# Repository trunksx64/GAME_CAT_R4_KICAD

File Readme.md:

# Game//Cat ::: Revisión R4 :: Versión 4.2.2

## Razón e Inspiración

El Game//Cat R4 es la evolución del microcontrolador de 16Bits a 32Bits, mas específicamente del PIC24H al ATSAMD21 como núcleo de control, al igual que su antecesor la idea de esta tarjeta y/ó control de desarrollo es usar dispositivos específicos para el aprendizaje, bricolaje y Hobby para proyectos abiertos o de diseño cerrado, el Hardware el Libre con la posibilidad de adaptarlo, modificarlo, cambiarlo a necesidad, claramente respetando al original. El ATSAMD21 es un microcontrolador Originalmente diseñado por ATMEL que utiliza un Nucleo ARM 0M+ dando la ventaja de ser un microcontrolador fácil de usar con Módulos flexibles y robustos, con documentación abundante tanto por lo Comunidad de ARDUINO y la empresa Microchip en este momento. Se diseñó empleando de forma similar la apariencia del Game//Cat R3, agregando mejoras y eliminando errores del anterior, por lo cual es 100% compatible a nivel de diseño.

El ATSAMD21 es compatible en este momento con Microchip Studio (Atmel Studio) y MPLABX V5.0, tanto con GCC y XC32, para programarlo se puede usar ATMEL ICE, MPLAB SNAP, PICKIT4 y El ICD4, Se planea usar el Bootloader original de ARDUINO Zero en un futuro.

Algunos Elementos "Footprints" y "Symbols" están basados en mis librerías, cuáles encontrarán en este mismo Repositorio.

## Características del Hardware

  * Microcontrolador ATSAMD21.
  * Pantalla LCD PCD8544 (Based Nokia GLCD) - SPI.
  * Joystick Análogo de 2 ejes + Botón Digital.
  * 6 Botones Digitales.
  * Accelerometro - MMA8452Q - I2C. 
  * Sensor de Temperatura (LM61).
  * Sensor de Luz (LDR).
  * Memoria Eeprom 24LCXXX - I2C.
  * Memoria Ram 23KXX - SPI.
  * Memoria Flash SST26VF032B - SPI.
  * Ranura Memoria Micro-SD - SPI.
  * Buzzer por PWM.
  * Conexión USB - Nativa por el ATSAM.
  * Conexión CAN-FD - MCP2518FD.
  * 2 LED´s de Actividad.
  * Salidas Para PWM y UART - Con figurables - 3.3V.
  * Conexión SWD Nativa para Debuger.
  * Cargador de Batería Lipo (MCP73831) con Indicador LED.
  * Regulación 3.3V mediante TPS54231.

## Características Específicas

* Para garantizar el control y tensión correspondiente para el uso de BUS CAN, se utiliza el Transeiver MCP2562FD en conjunto del CI MCP2518FD, haciendo compatible el Control con la última version del protocolo CAN.

* Para Potabilidad he agregado un control para la carga de Baterías de tipo Lipo, este gobernado él con el CI MCP73831, el cual intercambia la alimentación proveniente del conector USB y la Batería según el estado de conexión, se puede usar Baterías de 3,7V en adelante hasta un máximo de 6V, se agregó un interruptor para porder desconectar la Batería en modo portable, para evitar su descarga prologanda.

* Para el Manejo del Joystick, Botones, he empleado el CI-74HC4051, que es un Multiplexor Análogo para leer los Valores por el módulo ADC, el cual puede usarse de 10 o 12Bits en conjunto con un canal DMA si fuere necesario.

* La Comunicación por algunos de los Módulos SERCOM disponibles en los conectores Molex, posee un conversor de tensión de 3.3V a 5V de forma bidireccional con transistores Mosfet, con el fin de proteger y poder comunicar el ATSAMD21 con cualquier tipo de dispositivo.

* La Comunicación USB está dedicada por el mismo ATSAMD21, por lo que es necesario programar el Stack propio, este microcontrolador posee una enorme flexibilidad para configurar impactando de forma mínima los recursos. Es posible utilizar el Bootloader del Arduino Zero con algunas modificaciones, aún está en planes de creación, recomiendo emplear el código Generado por AMTEL START, para simplificar las configuraciones tanto de este Módulo como otros Periféricos.

* La Ranura para la Tarjeta Micro-SD, posee conexión Módulo SPI la cual esta compartida con la Memoria Ram 23Kxxx y Memoria Flash SST26VF032B, Además la pantalla posee también una conexión al segundo Módulo SPI, que puede usarse para "colgar" otros dispositivos si no vamos a usar la Pantalla.

* El control del Buzzer se ha dejado por un Pin que puede ser usado tanto por el Modulo PWM o un pin Común, su uso dependerá del Programa o Aplicación.

* Posee una Memoria I2C en conjunto con un Accelerometro, con comunicación directa.

* Los sensores de Luminosidad y Temperatura están conectados directamente a entradas Analógicas del ATSAMD21, no siendo necesario utilizar le MUX 74HC4051.

* La programación se hace por medio de la conexión ICSP o Bootloader por USB, empleando cualquier programador reciente como el ICD4, PICKIT4, SNAP o ATMEL ICE, igual estas salidas pueden usarse como cualquier puerto, teniendo presente que no poseen ninguna protección a tensiones superiores de 3,3V.

* Ya por Último, he dejado dos visualiza-dores, que usan los pines asignados para la Programación del ATSAMD21, controlados por Mosfets para no interferir con el protocolo SWD, su uso está condicionado fuera del Debug.

## Microcontrolador

  * Microcontrolador ATSAMD21 ARM 0M+ de 32Bits.
  * 256KB of flash and 32KB of SRAM.
  * Up to 48MHz operating frequency.
  * Six serial communication modules (SERCOM) configurable as UART/USART, SPI or I2C, three 16-bit timer/counters, 32-bit Real-Time Clock and calendar, 20 PWM channels, one 14-channel 12-bit ADC, one 10-bit DAC.
  * Full Speed USB Device and embedded Host.
  * 1.62V to 3.63V power supply.
  * Internal and external clock options with 48MH Digital Frequency Locked Loop (DFLL48M) and 48MHto 96MHFractional.
  * Two-pin Serial Wire Debug (SWD) programming, test and debugging interface.
  * 38 GPIO pins.
  * 10-bit, 350ksps Digital-to-Analog Converter (DAC).
  * CRC-32 generator.
  * 32-bit Real Time Counter (RTC) with clock/calendar function.
  * Generation of synchronized pulse width modulation (PWM) pattern across port pins.

## Versiones

* 2021 : 4.0.0 : Primera Versión de Diseño.
* 2021 : 4.0.1 : Mirgración completa a Kicad V6, actualización del Libreias y Logos de Diseño.
* 2021 : 4.1.0 : Cambio de Botones Pasantes a SDM.
* 2021 : 4.1.2 : Conectores Moles de tres pines a cuatro pines para Alimentación externar de dispositivos.
* 2021 : 4.1.3 : Correción y cambio de puerto de Programación SWD RJ11 a Header 2x3, similar al AVR SPI.
* 2021 : 4.1.4 : Cambio de Resistencias del conversor de nivel 5V-3.3V de 1K a 10K.
* 2022 : 4.1.5 : Se agregó Interruptor de Encendio por Batería con control Mosfet.
* 2024 : 4.1.6 : Se Elimia Resistencia de Pull para la Linea SWCLK.
* 2024 : 4.1.8 : Se Elimia Diodo del Control de Batería del control Mosfet
* 2025 : 4.2.2 : Se Corrige Mosfet de los LEDs de Estado y Conexion del BUS I2C.

## Créditos

xDNA Electronics & Desing es una Micro-empresa Personal, que se dedica y encarga de elaborar proyectos de Control y Automatización por pedido, su idea es colaborar y ayudar a quines a si lo requieran, el proyecto se hizo principalmente como Hobby el cual gracias a terceros se pudo implementar y hacer su creación, por lo cual se da la libertad de usarlo para experimentar sin hacer uso comercial del mismo.

## Licencia

Licensed under Attribution-NonCommercial-ShareAlike 4.0 International (CC BY-NC-SA 4.0)

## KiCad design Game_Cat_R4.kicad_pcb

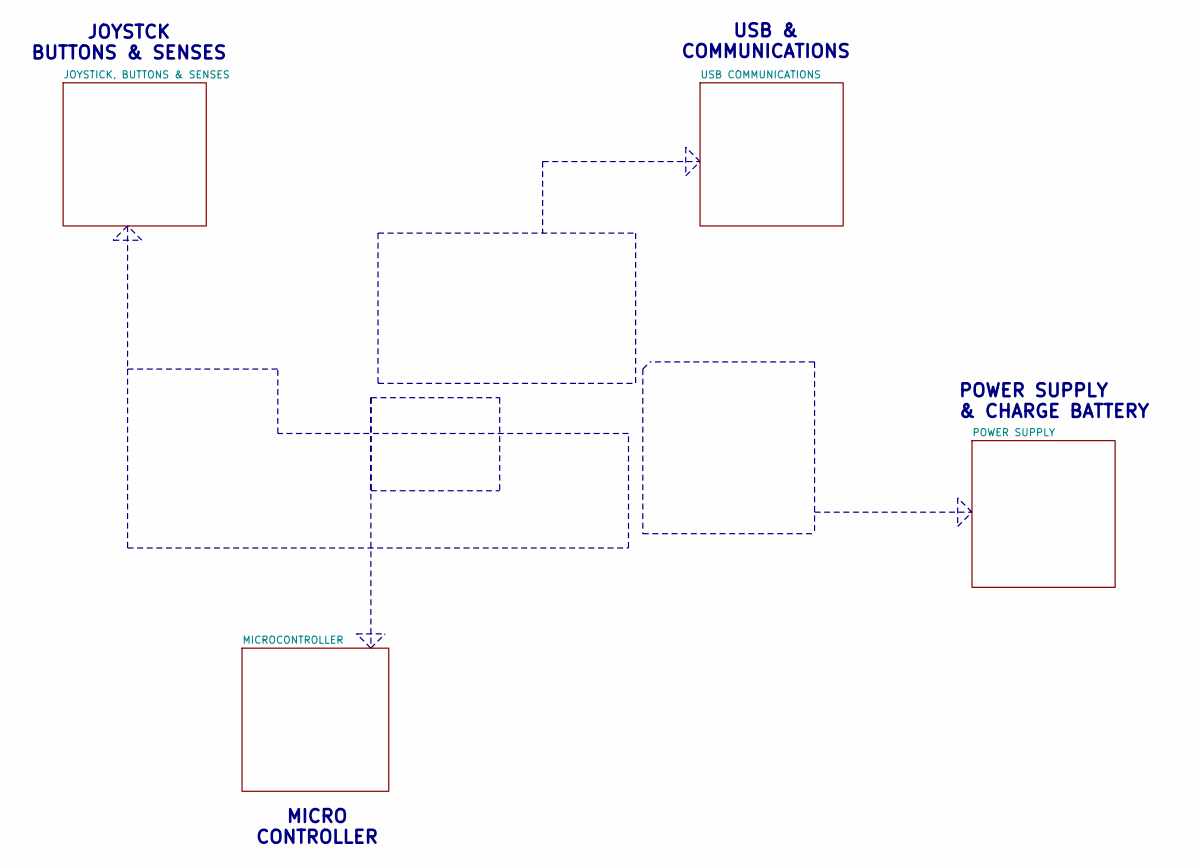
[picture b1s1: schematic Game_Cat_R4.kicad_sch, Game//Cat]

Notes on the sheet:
POWER SUPPLY & CHARGE BATTERY
MICRO CONTROLLER
USB & COMMUNICATIONS
JOYSTCK BUTTONS & SENSES

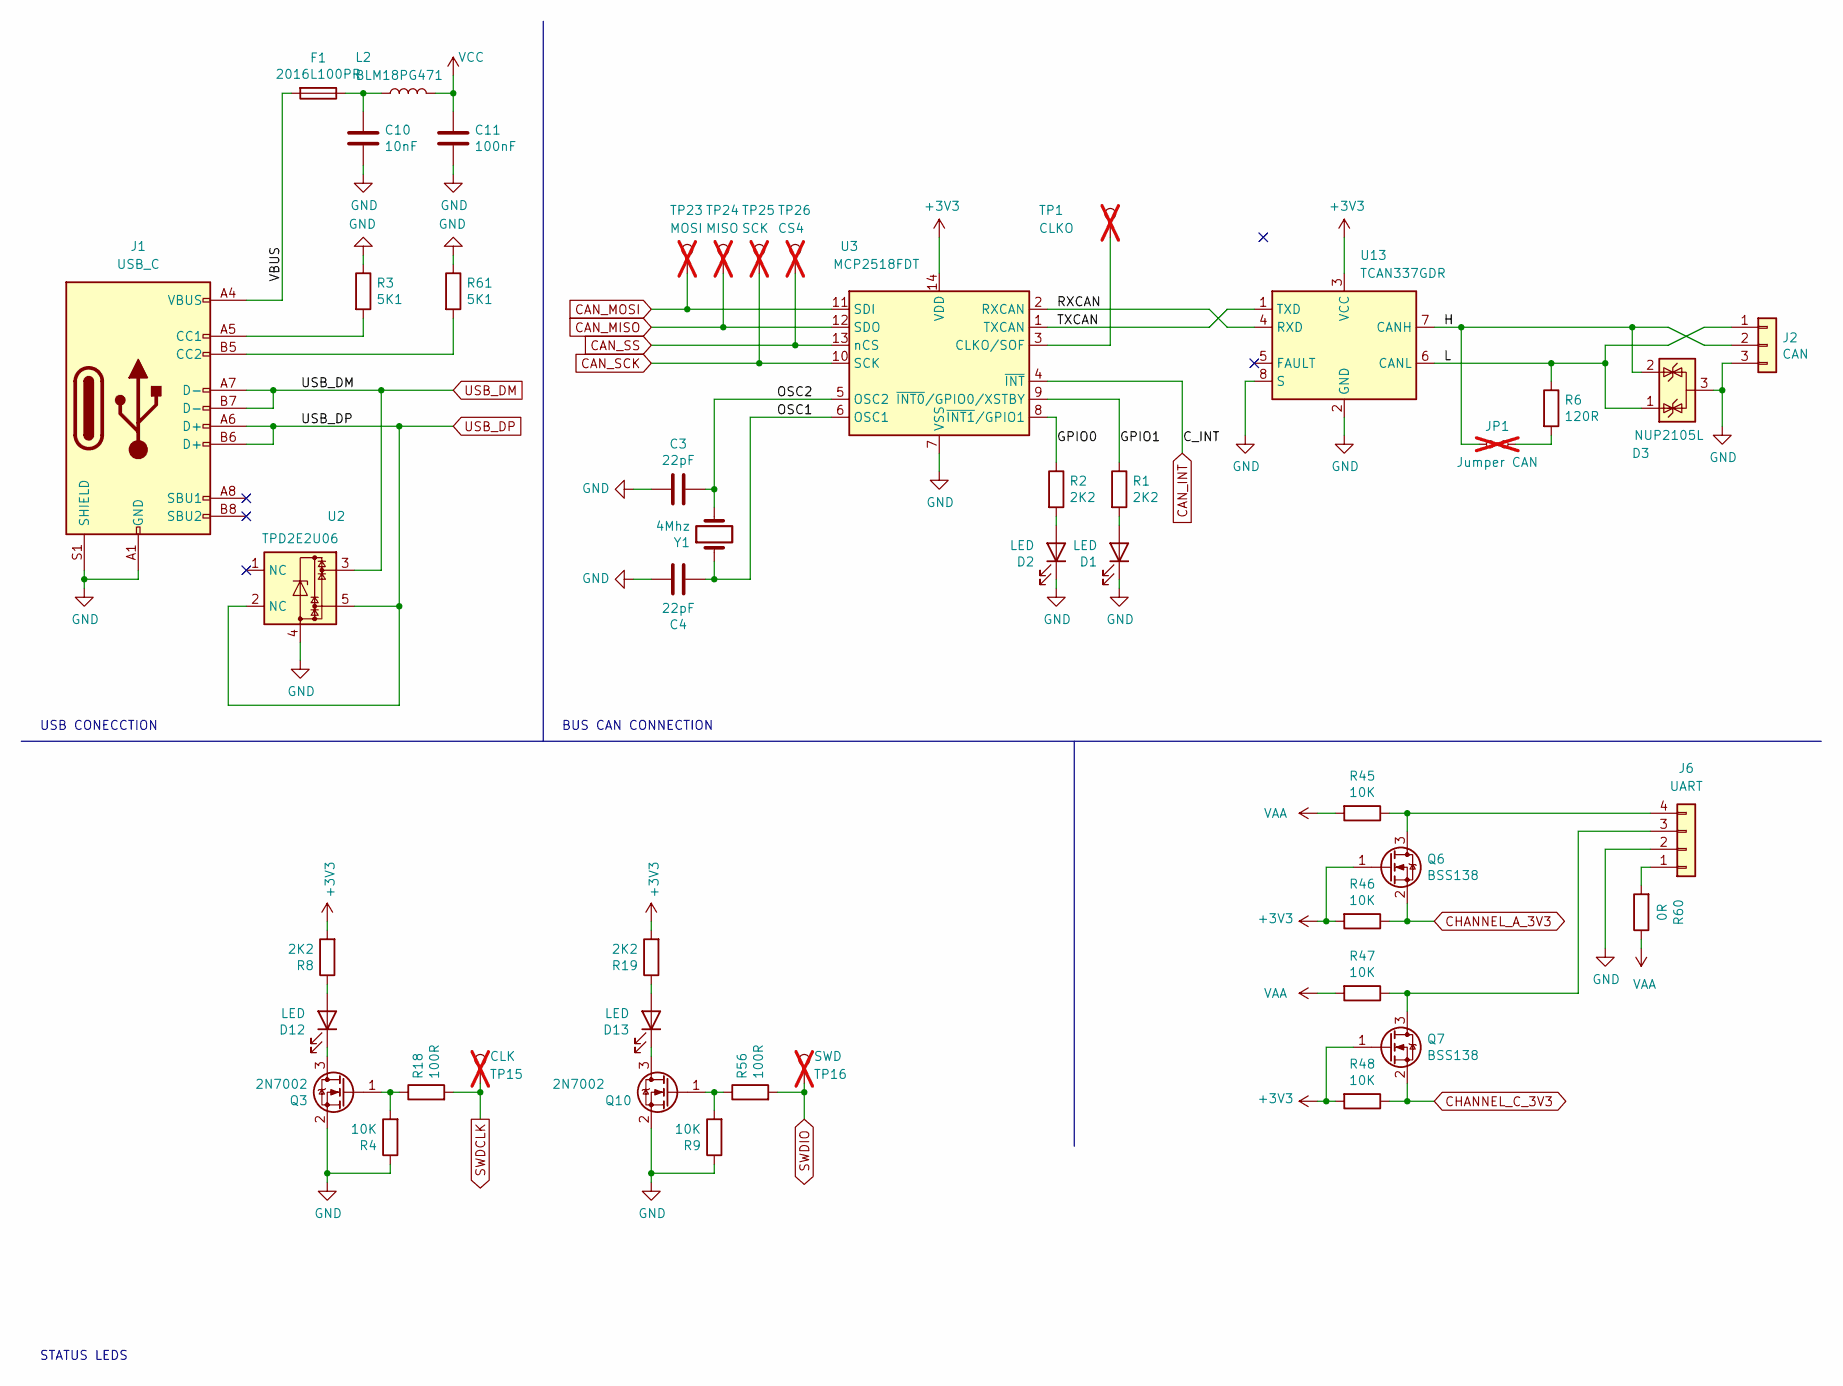
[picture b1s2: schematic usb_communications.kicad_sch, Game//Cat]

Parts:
C3, C4: 22pF; C_0805_2012Metric; Digikey C0805C220J5GAC7800
C10: 10nF; C_1206_3216Metric; Digikey GRM3195C1H113JA01D
C11: 100nF; C_1206_3216Metric; Digikey C3216X7R2E104K160AE
D1, D2, D12, D13: LED; LED_0805_2012Metric; Digikey LTST-C170GKT
D3: NUP2105L; SOT-23; Digikey NUP2105L
F1: 2016L100PR; MF_SMDF200; Digikey 2016L100PR
J1: USB_C; USB_C_HRO_TYPE-C-31-M-12; Digikey 12402012E212A
J2: CAN; MOLEX_KK_1x03_P2.54mm_HORIZONTAL; Digikey SWR25X-NRTC-S03-RB-BA
J6: UART; MOLEX_KK_1x04_P2.54mm_HORIZONTAL; Digikey SWR25X-NRTC-S04-RB-BA
JP1: Jumper CAN; SolderJumper-2_P1.3mm_Open_RoundedPad1.0x1.5mm; Digikey M20-9990245; not fitted
L2: BLM18PG471; L_1206_3216Metric; Digikey BLM18PG471SZ1D
Q3, Q10: 2N7002; SOT-23; Digikey 2N7002
Q6, Q7: BSS138; SOT-23; Digikey BSS138
R1, R2, R8, R19: 2K2; R_1206_3216Metric; Digikey RC1206FR-072K2L
R3, R61: 5K1; R_1206_3216Metric; Digikey RC1206FR-075K1L
R4, R9, R45, R46, R47, R48: 10K; R_1206_3216Metric; Digikey RC1206FR-0710KL
R6: 120R; R_1206_3216Metric; Digikey RC1206JR-07120RL
R18, R56: 100R; R_1206_3216Metric; Digikey RC1206JR-07100RL
R60: 0R; R_1206_3216Metric; Digikey RC1206FR-0710KL
TP1: CLKO; TestPoint_Pad_D1.0mm; not fitted
TP15: CLK; TestPoint_Pad_D1.0mm; not fitted
TP16: SWD; TestPoint_Pad_D1.0mm; not fitted
TP23: MOSI; TestPoint_Pad_D1.0mm; not fitted
TP24: MISO; TestPoint_Pad_D1.0mm; not fitted
TP25: SCK; TestPoint_Pad_D1.0mm; not fitted
TP26: CS4; TestPoint_Pad_D1.0mm; not fitted
U2: TPD2E2U06; SOT-23-5; Digikey TPD2E2U06DRLR
U3: MCP2518FDT; SOIC-14_3.9x8.7mm_P1.27mm; Digikey MCP2518FDT-H/SL
U13: TCAN337GDR; SOIC-8_3.9x4.9mm_P1.27mm; Digikey TCAN337GDR
Y1: 4Mhz; ECS_160_20_3X_TR; Digikey ECS-200-CDX-0914

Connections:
+3V3: Q6.1 (G), Q7.1 (G), R8.2, R19.2, R46.2, R48.2, U3.14 (VDD), U13.3 (VCC); also elsewhere on the board
/USB COMMUNICATIONS/GPIO0: R2.1, U3.8 (~INT1/GPIO1)
/USB COMMUNICATIONS/GPIO1: R1.1, U3.9 (~INT0/GPIO0/XSTBY)
/USB COMMUNICATIONS/H: D3.2 (K), J2.2, JP1.1, U13.7 (CANH)
/USB COMMUNICATIONS/L: D3.1 (K), J2.1, R6.1, U13.6 (CANL)
/USB COMMUNICATIONS/OSC1: C4.2, U3.6 (OSC1), Y1.1
/USB COMMUNICATIONS/OSC2: C3.2, U3.5 (OSC2), Y1.2
/USB COMMUNICATIONS/RXCAN: U3.2 (RXCAN), U13.4 (RXD)
/USB COMMUNICATIONS/TXCAN: U3.1 (TXCAN), U13.1 (TXD)
/USB COMMUNICATIONS/VBUS: F1.2, J1.A4 (VBUS), J1.A9 (VBUS), J1.B4 (VBUS), J1.B9 (VBUS)
CAN_INT: U3.4 (~INT); also elsewhere on the board
CAN_MISO: TP24.1, U3.12 (SDO); also elsewhere on the board
CAN_MOSI: TP23.1, U3.11 (SDI); also elsewhere on the board
CAN_SCK: TP25.1, U3.10 (SCK); also elsewhere on the board
CAN_SS: TP26.1, U3.13 (nCS); also elsewhere on the board
CHANNEL_A_3V3: Q6.2 (S), R46.1; also elsewhere on the board
CHANNEL_C_3V3: Q7.2 (S), R48.1; also elsewhere on the board
GND: C3.1, C4.1, C10.2, C11.2, D1.1 (K), D2.1 (K), D3.3 (A), J1.A1 (GND), J1.A12 (GND), J1.B1 (GND), J1.B12 (GND), J1.S1 (SHIELD), J2.3, J6.2, Q3.2 (S), Q10.2 (S), R3.1, R4.1, R9.1, R61.1, U2.4, U3.7 (VSS), U13.2 (GND), U13.8 (S); also elsewhere on the board
unnamed: C10.1, F1.1, L2.1
unnamed: D1.2 (A), R1.2
unnamed: D2.2 (A), R2.2
unnamed: D12.2 (A), R8.1
unnamed: D12.1 (K), Q3.3 (D)
unnamed: D13.2 (A), R19.1
unnamed: D13.1 (K), Q10.3 (D)
unnamed: J1.A5 (CC1), R3.2
unnamed: J1.B5 (CC2), R61.2
unnamed: J6.1, R60.2
unnamed: J6.3, Q7.3 (D), R47.1
unnamed: J6.4, Q6.3 (D), R45.1
unnamed: JP1.2, R6.2
unnamed: Q3.1 (G), R4.2, R18.1
unnamed: Q10.1 (G), R9.2, R56.1
unnamed: TP1.1, U3.3 (CLKO/SOF)
SWDCLK: R18.2, TP15.1; also elsewhere on the board
SWDIO: R56.2, TP16.1; also elsewhere on the board
USB_DM: J1.A7 (D-), J1.B7 (D-), U2.3; also elsewhere on the board
USB_DP: J1.A6 (D+), J1.B6 (D+), U2.2 (NC), U2.5; also elsewhere on the board
VAA: R45.2, R47.2, R60.1; also elsewhere on the board
VCC: C11.1, L2.2; also elsewhere on the board

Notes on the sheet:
BUS CAN CONNECTION
STATUS LEDS
USB CONECCTION

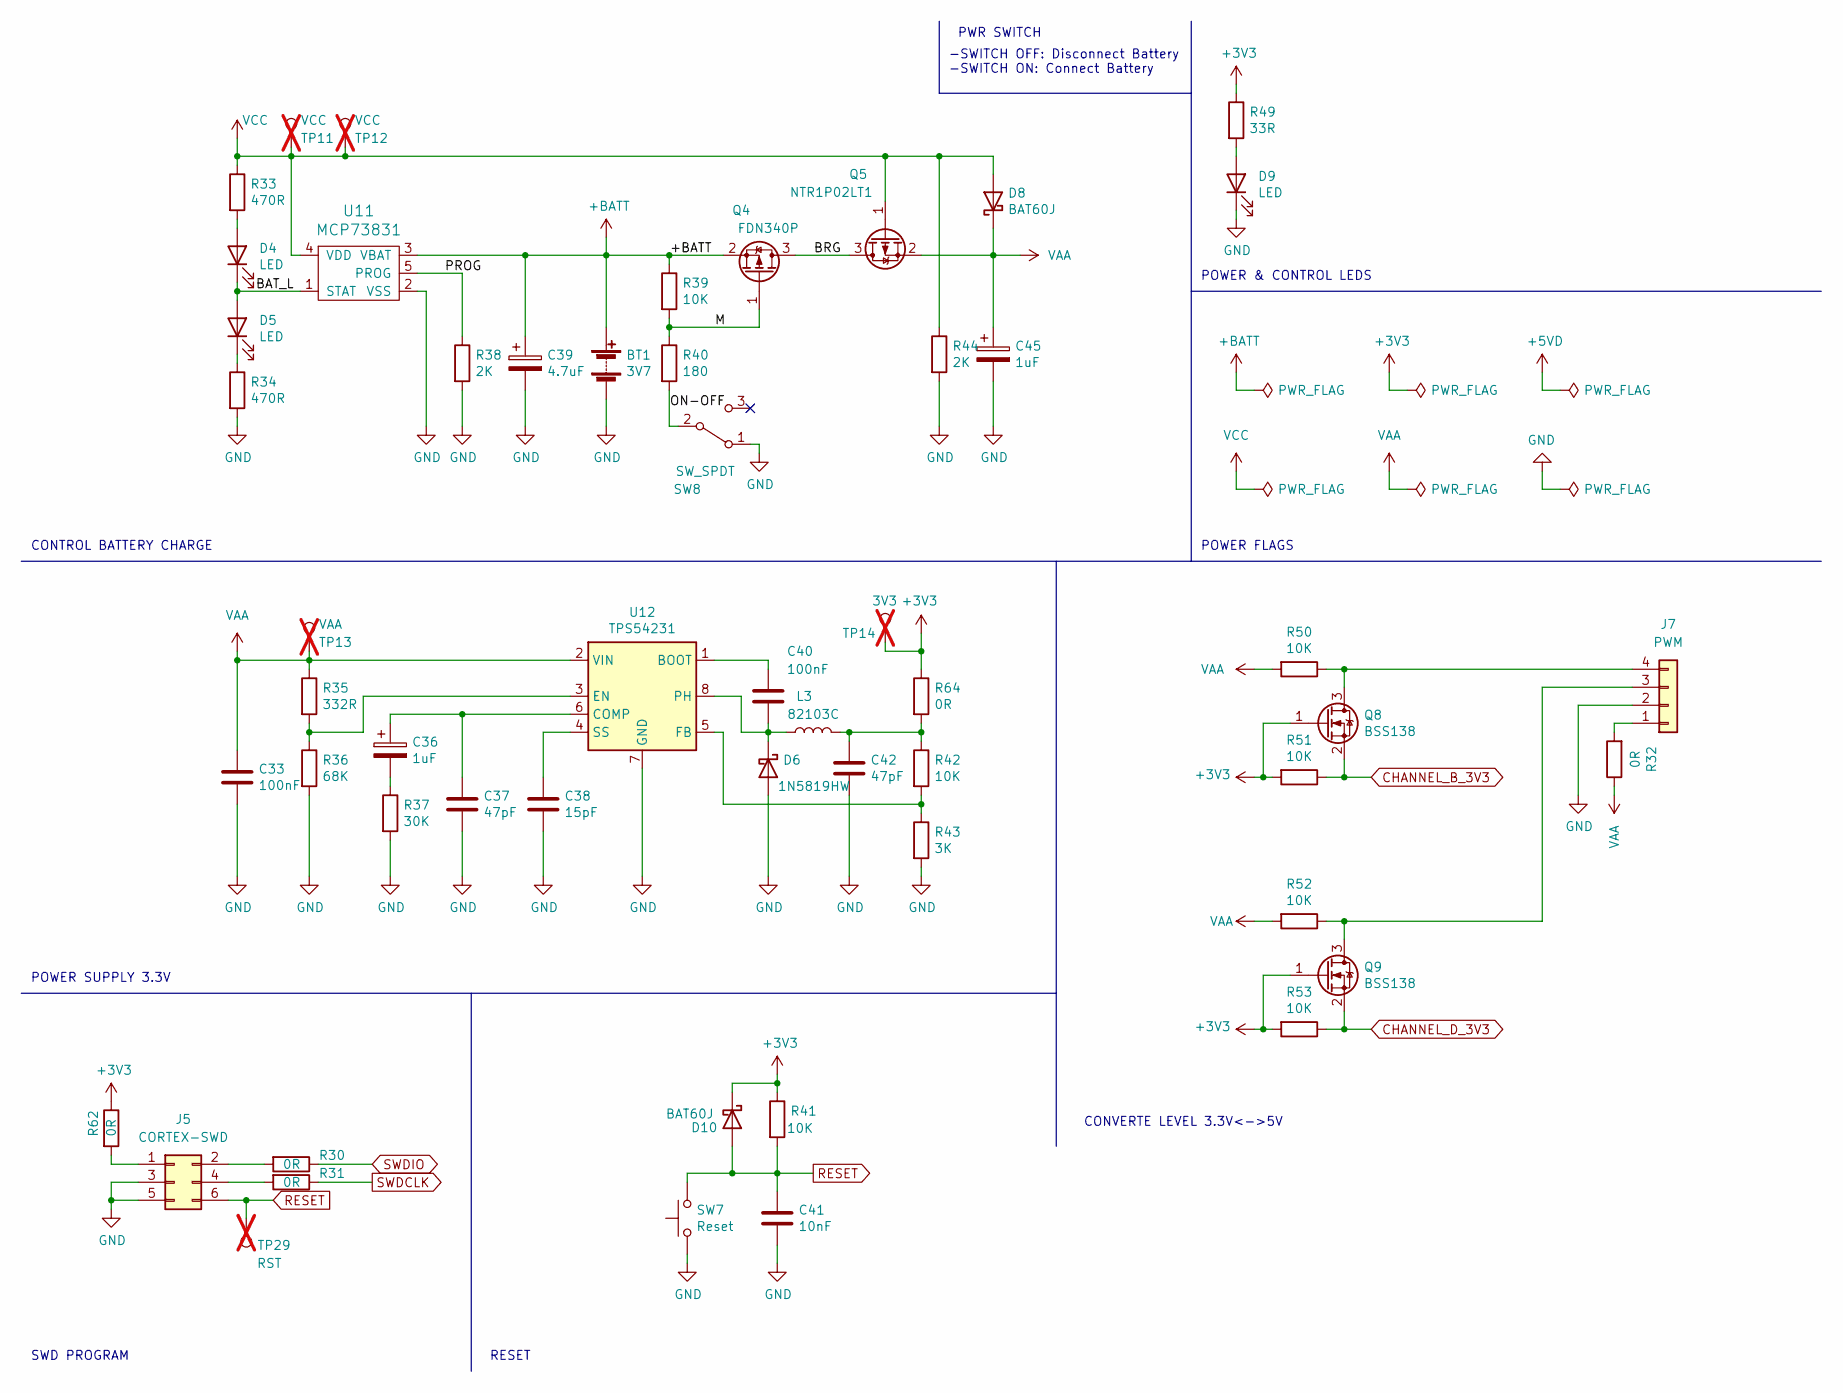
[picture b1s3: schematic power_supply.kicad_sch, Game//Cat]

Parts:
BT1: 3V7; S2B_PH_SM4_TB; Digikey S2B-PH-SM4-TB
C33, C40: 100nF; C_1206_3216Metric; Digikey C3216X7R2E104K160AE
C36, C45: 1uF; CP_EIA-3216-18_Kemet-A; Digikey TAJA105K016RNJ
C37: 47pF; C_0805_2012Metric; Digikey GRM21A5C2E470JW01D
C38: 15pF; C_1206_3216Metric; Digikey GCM31A5C3A150FX01D
C39: 4.7uF; CP_EIA-3216-18_Kemet-A; Digikey TAJA475K016RNJ
C41: 10nF; C_1206_3216Metric; Digikey GRM3195C1H113JA01D
C42: 47pF; C_1206_3216Metric; Digikey GCM31A5C3A470FX01D
D4, D5, D9: LED; LED_0805_2012Metric; Digikey LTST-C170GKT
D6: 1N5819HW; D_SOD-123; Digikey 1N5819HWQ-7-F
D8, D10: BAT60J; D_SOD-323_HandSoldering; Digikey BAT60JFILM
J5: CORTEX-SWD; IDC-Header_2x03_P2.54mm_Horizontal; Digikey 61200621721
J7: PWM; MOLEX_KK_1x04_P2.54mm_HORIZONTAL; Digikey SWR25X-NRTC-S04-RB-BA
L3: 82103C; L_Murata_82103C; Digikey 82103C
Q4: FDN340P; SOT-23; Digikey FDN340P
Q5: NTR1P02LT1; SOT-23; Digikey NTR1P02LT1G
Q8, Q9: BSS138; SOT-23; Digikey BSS138
R30, R31, R32, R62, R64: 0R; R_1206_3216Metric; Digikey RC1206FR-0710KL
R33, R34: 470R; R_1206_3216Metric; Digikey RC1206JR-07470RL
R35: 332R; R_1206_3216Metric; Digikey RC1206FR-07332RL
R36: 68K; R_1206_3216Metric; Digikey RC1206FR-0768KL
R37: 30K; R_1206_3216Metric; Digikey RC1206FR-0730KL
R38, R44: 2K; R_1206_3216Metric; Digikey RC1206FR-072KL
R39, R41, R42, R50, R51, R52, R53: 10K; R_1206_3216Metric; Digikey RC1206FR-0710KL
R40: 180; R_1206_3216Metric; Digikey RC1206JR-07180RL
R43: 3K; R_1206_3216Metric; Digikey RC1206FR-073KL
R49: 33R; R_1206_3216Metric; Digikey RC1206JR-0733RL
SW7: Reset; SW_PUSH_6mm_H5mm; Digikey PTS645SK50SMTR92 LFS
SW8: SW_SPDT; SW_SPDT_PCM12; Digikey PCM12SMTR
TP11, TP12: VCC; TestPoint_Pad_D1.0mm; not fitted
TP13: VAA; TestPoint_Pad_D1.0mm; not fitted
TP14: 3V3; TestPoint_Pad_D1.0mm; not fitted
TP29: RST; TestPoint_Pad_D1.0mm; not fitted
U11: MCP73831; SOT-23-5; Digikey MCP73831T-5ACI/OT
U12: TPS54231; SOIC-8_3.9x4.9mm_P1.27mm; Digikey TPS54231D

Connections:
+3V3: D10.1 (K), Q8.1 (G), Q9.1 (G), R41.1, R49.1, R51.2, R53.2, R62.1, R64.1, TP14.1; also elsewhere on the board
+BATT: BT1.1 (+), C39.1, Q4.2 (S), R39.1, U11.3 (VBAT)
/POWER SUPPLY/BAT_L: D4.1 (K), D5.2 (A), U11.1 (STAT)
/POWER SUPPLY/BRG: Q4.3 (D), Q5.3 (D); also elsewhere on the board
/POWER SUPPLY/M: Q4.1 (G), R39.2, R40.1; also elsewhere on the board
/POWER SUPPLY/ON-OFF: R40.2, SW8.2 (B)
/POWER SUPPLY/PROG: R38.1, U11.5 (PROG)
CHANNEL_B_3V3: Q8.2 (S), R51.1; also elsewhere on the board
CHANNEL_D_3V3: Q9.2 (S), R53.1; also elsewhere on the board
GND: BT1.2 (-), C33.2, C37.2, C38.2, C39.2, C41.2, C42.2, C45.2, D6.2 (A), D9.1 (K), J5.3, J5.5, J7.2, R34.2, R36.2, R37.2, R38.2, R43.2, R44.2, SW7.1, SW8.1 (A), U11.2 (VSS), U12.7 (GND); also elsewhere on the board
unnamed: C36.2, R37.1
unnamed: C42.1, L3.2, R42.1, R64.2
unnamed: D4.2 (A), R33.2
unnamed: D5.1 (K), R34.1
unnamed: C40.2, D6.1 (K), L3.1, U12.8 (PH)
unnamed: D9.2 (A), R49.2
unnamed: J5.1, R62.2
unnamed: J5.2, R30.2
unnamed: J5.4, R31.2
unnamed: J7.1, R32.2
unnamed: J7.3, Q9.3 (D), R52.1
unnamed: J7.4, Q8.3 (D), R50.1
unnamed: C40.1, U12.1 (BOOT)
unnamed: C36.1, C37.1, U12.6 (COMP)
unnamed: R35.2, R36.1, U12.3 (EN)
unnamed: R42.2, R43.1, U12.5 (FB)
unnamed: C38.1, U12.4 (SS)
RESET: C41.1, D10.2 (A), J5.6, R41.2, SW7.2, TP29.1; also elsewhere on the board
SWDCLK: R31.1; also elsewhere on the board
SWDIO: R30.1; also elsewhere on the board
VAA: C33.1, C45.1, D8.1 (K), Q5.2 (S), R32.1, R35.1, R50.2, R52.2, TP13.1, U12.2 (VIN); also elsewhere on the board
VCC: D8.2 (A), Q5.1 (G), R33.1, R44.1, TP11.1, TP12.1, U11.4 (VDD); also elsewhere on the board

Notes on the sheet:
CONTROL BATTERY CHARGE
PWR SWITCH
POWER SUPPLY 3.3V
CONVERTE LEVEL 3.3V<->5V
POWER FLAGS
-SWITCH OFF: Disconnect Battery -SWITCH ON: Connect Battery
POWER & CONTROL LEDS
RESET
SWD PROGRAM

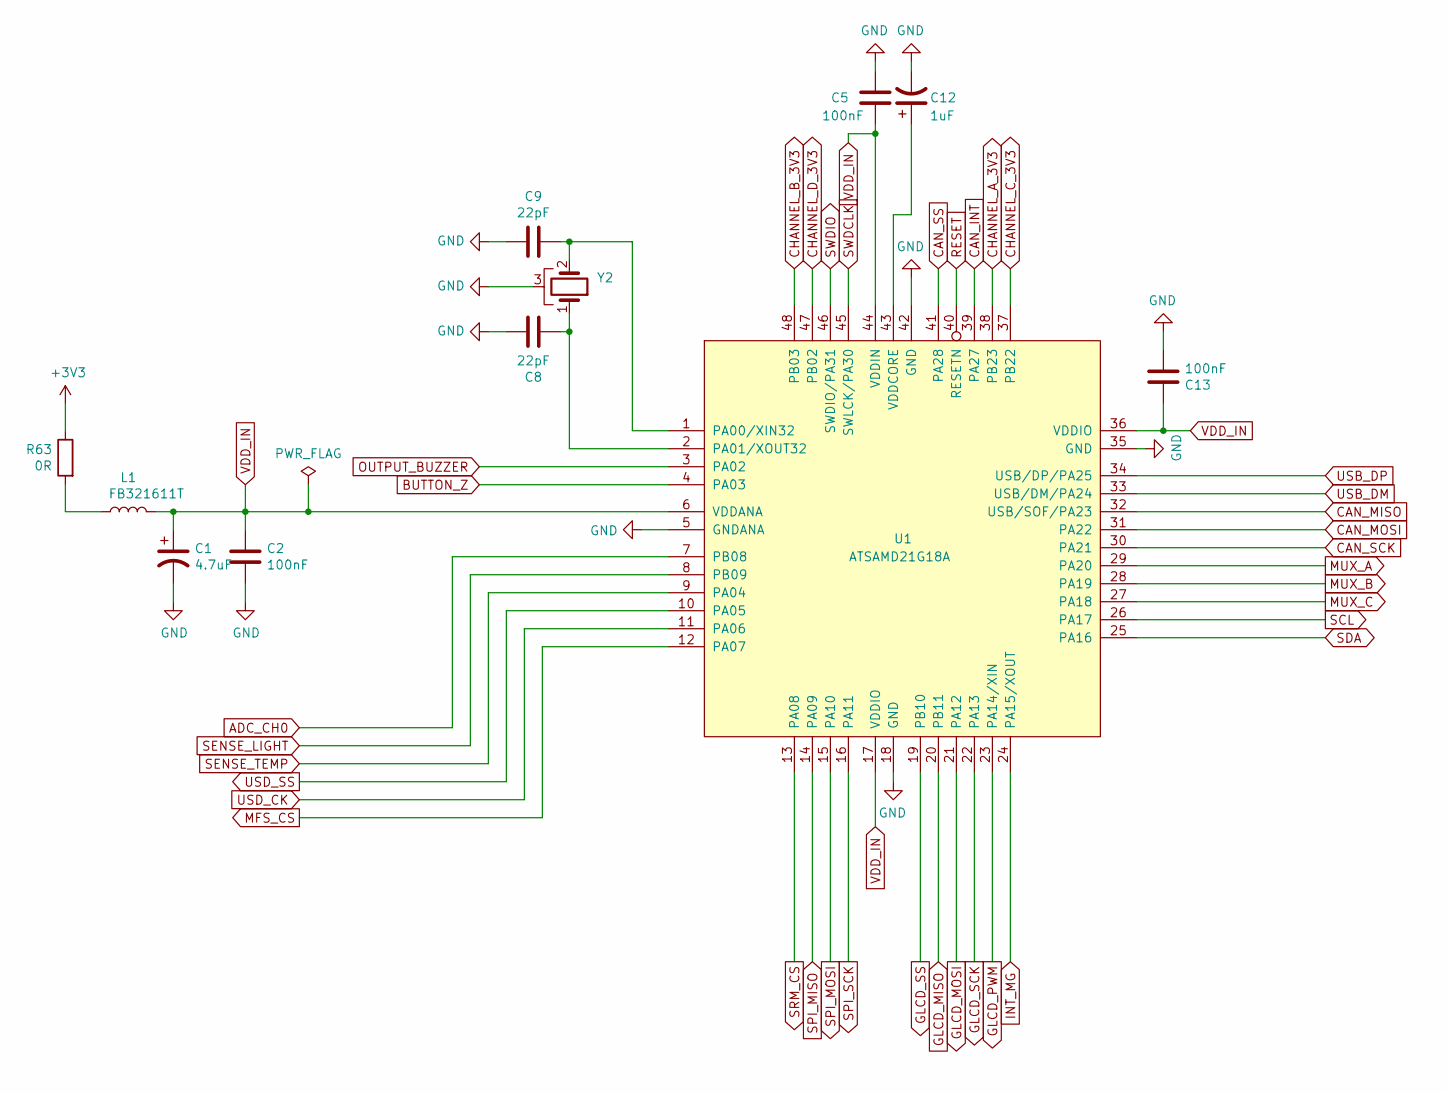
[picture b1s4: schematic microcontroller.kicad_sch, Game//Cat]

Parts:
C1: 4.7uF; CP_EIA-3216-18_Kemet-A; Digikey TAJA475K016RNJ
C2, C5, C13: 100nF; C_1206_3216Metric; Digikey C3216X7R2E104K160AE
C8, C9: 22pF; C_0805_2012Metric; Digikey C0805C220J5GAC7800
C12: 1uF; CP_EIA-3216-18_Kemet-A; Digikey TAJA105K016RNJ
L1: FB321611T; L_1206_3216Metric; Digikey FB321611T-260Y-S
R63: 0R; R_1206_3216Metric; Digikey RC1206FR-0710KL
U1: ATSAMD21G18A; TQFP-48_7x7mm_P0.5mm; Digikey ATSAMD21G18A-AU
Y2: Crystal_GND3; MS1V_T1K_32.768KHZ_7PF_20PPM_TA; Digikey MS1V-T1K-32.768KHZ-9PF-20PPM-TA-QC

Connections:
+3V3: R63.1; also elsewhere on the board
ADC_CH0: U1.7 (PB08); also elsewhere on the board
BUTTON_Z: U1.4 (PA03); also elsewhere on the board
CAN_INT: U1.39 (PA27); also elsewhere on the board
CAN_MISO: U1.32 (USB/SOF/PA23); also elsewhere on the board
CAN_MOSI: U1.31 (PA22); also elsewhere on the board
CAN_SCK: U1.30 (PA21); also elsewhere on the board
CAN_SS: U1.41 (PA28); also elsewhere on the board
CHANNEL_A_3V3: U1.38 (PB23); also elsewhere on the board
CHANNEL_B_3V3: U1.48 (PB03); also elsewhere on the board
CHANNEL_C_3V3: U1.37 (PB22); also elsewhere on the board
CHANNEL_D_3V3: U1.47 (PB02); also elsewhere on the board
GLCD_MISO: U1.20 (PB11); also elsewhere on the board
GLCD_MOSI: U1.21 (PA12); also elsewhere on the board
GLCD_PWM: U1.23 (PA14/XIN); also elsewhere on the board
GLCD_SCK: U1.22 (PA13); also elsewhere on the board
GLCD_SS: U1.19 (PB10); also elsewhere on the board
GND: C1.2, C2.2, C5.2, C8.1, C9.1, C12.2, C13.2, U1.5 (GNDANA), U1.18 (GND), U1.35 (GND), U1.42 (GND), Y2.3; also elsewhere on the board
INT_MG: U1.24 (PA15/XOUT); also elsewhere on the board
MFS_CS: U1.12 (PA07); also elsewhere on the board
MUX_A: U1.29 (PA20); also elsewhere on the board
MUX_B: U1.28 (PA19); also elsewhere on the board
MUX_C: U1.27 (PA18); also elsewhere on the board
unnamed: L1.1, R63.2
unnamed: C9.2, U1.1 (PA00/XIN32), Y2.2
unnamed: C8.2, U1.2 (PA01/XOUT32), Y2.1
unnamed: C12.1, U1.43 (VDDCORE)
OUTPUT_BUZZER: U1.3 (PA02); also elsewhere on the board
RESET: U1.40 (RESETN); also elsewhere on the board
SCL: U1.26 (PA17); also elsewhere on the board
SDA: U1.25 (PA16); also elsewhere on the board
SENSE_LIGHT: U1.8 (PB09); also elsewhere on the board
SENSE_TEMP: U1.9 (PA04); also elsewhere on the board
SPI_MISO: U1.14 (PA09); also elsewhere on the board
SPI_MOSI: U1.15 (PA10); also elsewhere on the board
SPI_SCK: U1.16 (PA11); also elsewhere on the board
SRM_CS: U1.13 (PA08); also elsewhere on the board
SWDCLK: U1.45 (SWLCK/PA30); also elsewhere on the board
SWDIO: U1.46 (SWDIO/PA31); also elsewhere on the board
USB_DM: U1.33 (USB/DM/PA24); also elsewhere on the board
USB_DP: U1.34 (USB/DP/PA25); also elsewhere on the board
USD_CK: U1.11 (PA06); also elsewhere on the board
USD_SS: U1.10 (PA05); also elsewhere on the board
VDD_IN: C1.1, C2.1, C5.1, C13.1, L1.2, U1.6 (VDDANA), U1.17 (VDDIO), U1.36 (VDDIO), U1.44 (VDDIN)

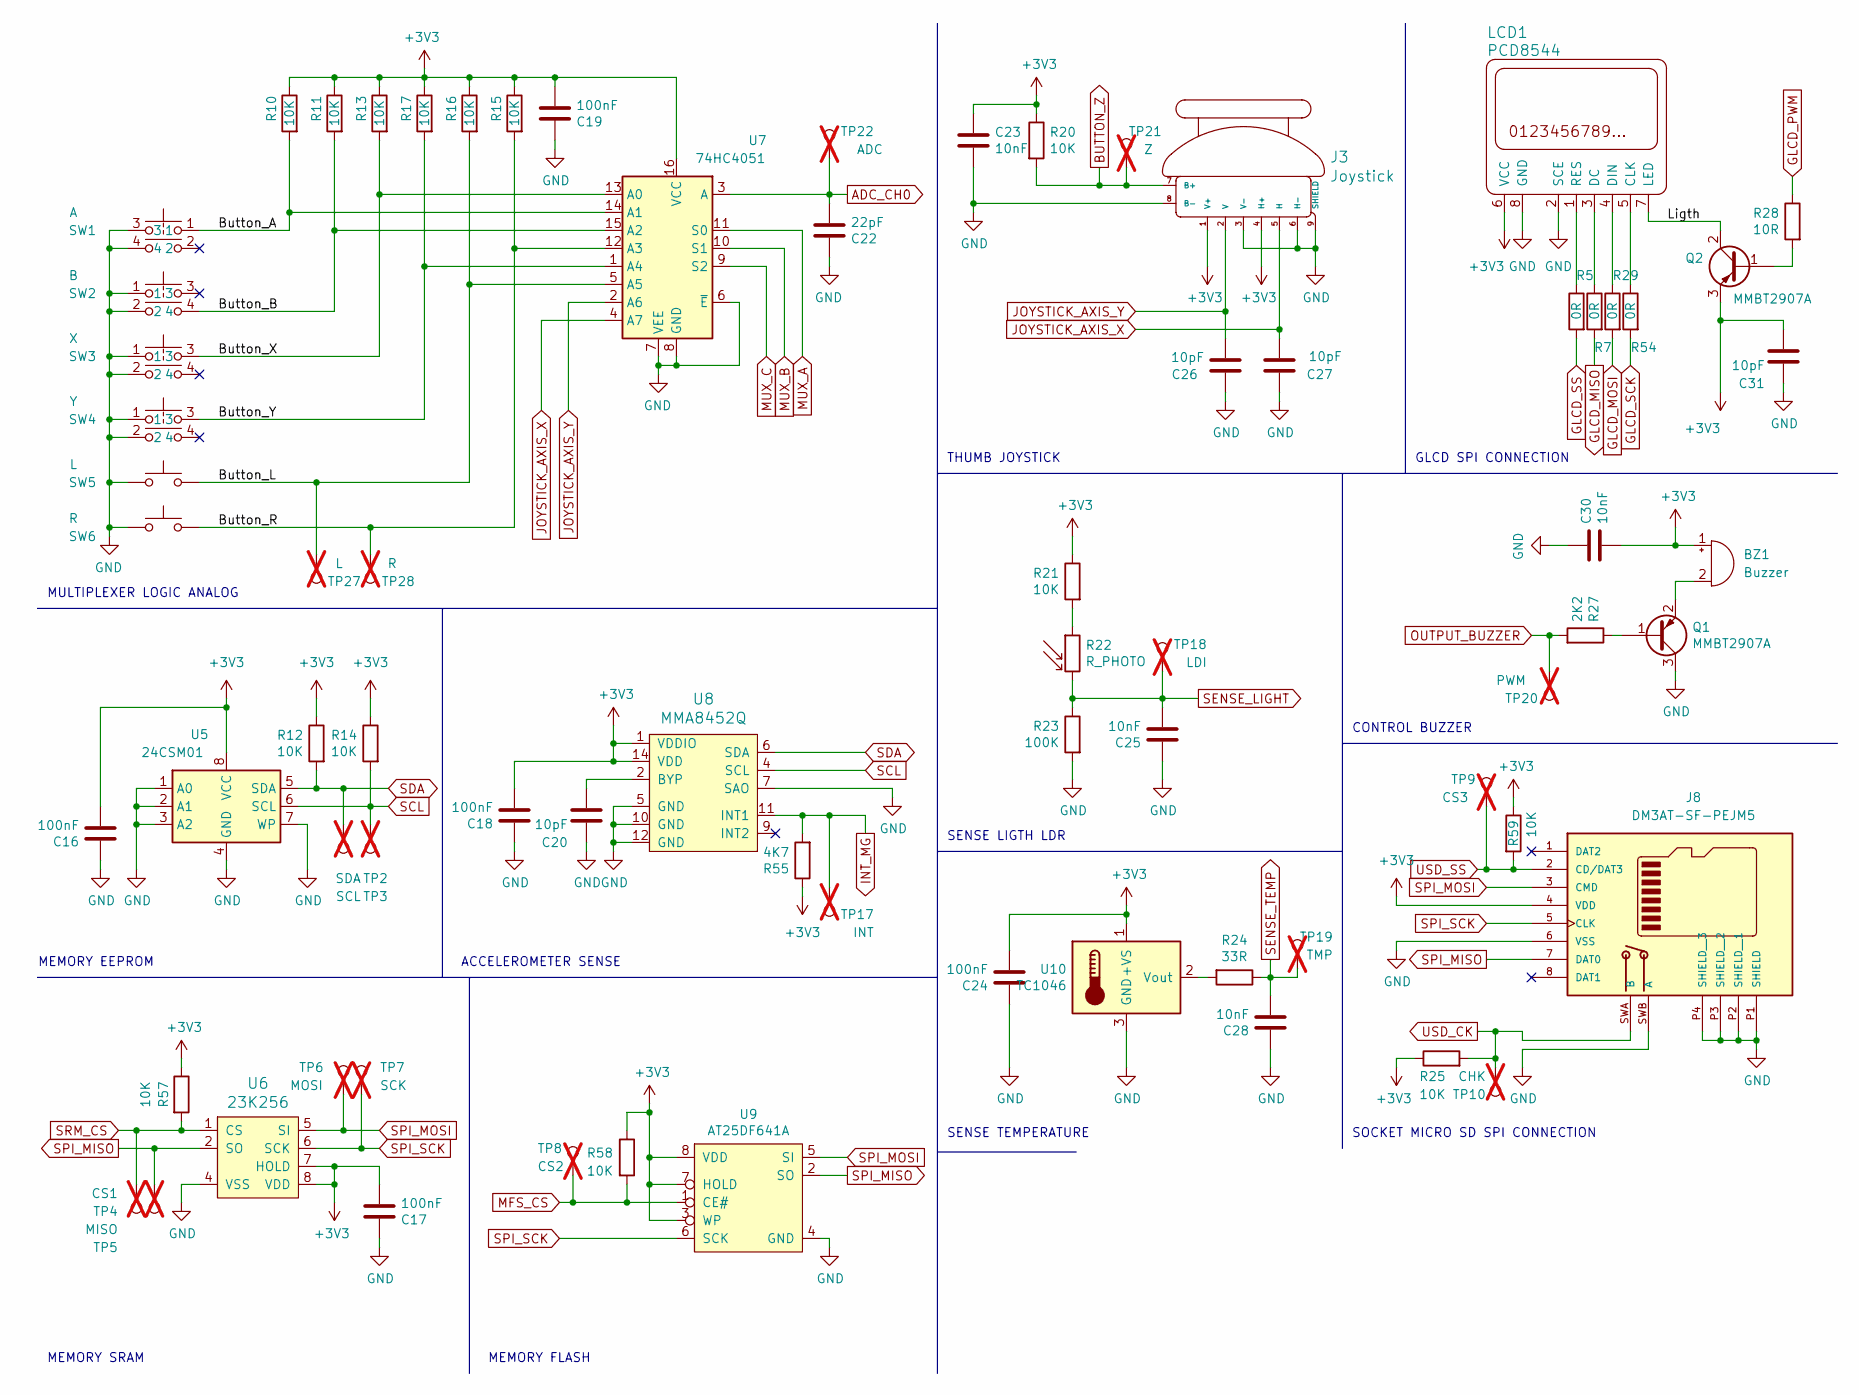
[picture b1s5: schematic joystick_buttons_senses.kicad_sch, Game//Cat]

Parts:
BZ1: Buzzer; AT_1224_TWT_5V_2_R; Digikey AI-1223-TWT-3V-2-R
C16, C17, C18, C19, C24: 100nF; C_1206_3216Metric; Digikey C3216X7R2E104K160AE
C20, C26, C27, C31: 10pF; C_0805_2012Metric; Digikey GRM21A5C2E100JW01D
C22: 22pF; C_0805_2012Metric; Digikey C0805C220J5GAC7800
C23, C25, C28, C30: 10nF; C_1206_3216Metric; Digikey GRM3195C1H113JA01D
J3: Joystick; JOYSTICK_TUMB; Digikey 09032
J8: DM3AT-SF-PEJM5; DM3AT_SF_PEJM5; Digikey DM3AT-SF-PEJM5
LCD1: PCD8544; GLCD_PCD8544_BASE; Digikey SSW-108-01-F-S
Q1, Q2: MMBT2907A; SOT-23; Digikey MMBT2907A-7-F
R5, R7, R29, R54: 0R; R_1206_3216Metric; Digikey RC1206FR-0710KL
R10, R11, R12, R13, R14, R15, R16, R17, R20, R21, R25, R57, R58, R59: 10K; R_1206_3216Metric; Digikey RC1206FR-0710KL
R22: R_PHOTO; PHOTO_CELL_VT900; Digikey N5AC501085
R23: 100K; R_1206_3216Metric; Digikey RC1206FR-07100KL
R24: 33R; R_1206_3216Metric; Digikey RC1206JR-0733RL
R27: 2K2; R_1206_3216Metric; Digikey RC1206FR-072K2L
R28: 10R; R_1206_3216Metric; Digikey RC1206FR-0710RL
R55: 4K7; R_1206_3216Metric; Digikey RC1206FR-074K7L
SW1: A; SWITCH_TACTILE_SPST_PLUNGER_CAP_GREEN_12x12mm_SMD; Digikey TL3300AF160Q
SW2: B; SWITCH_TACTILE_SPST_PLUNGER_CAP_RED_12x12mm_SMD; Digikey TL3300AF160Q
SW3: X; SWITCH_TACTILE_SPST_PLUNGER_CAP_BLUE_12x12mm_SMD; Digikey TL3300AF160Q
SW4: Y; SWITCH_TACTILE_SPST_PLUNGER_CAP_YELLOW_12x12mm_SMD; Digikey TL3300AF160Q
SW5: L; SW_Tactile_SPST_Angled_PTS645Vx58-2LFS; Digikey CT1102V3.85F160
SW6: R; SW_Tactile_SPST_Angled_PTS645Vx58-2LFS; Digikey CT1102V3.85F160
TP2: SDA; TestPoint_Pad_D1.0mm; not fitted
TP3: SCL; TestPoint_Pad_D1.0mm; not fitted
TP4: CS1; TestPoint_Pad_D1.0mm; not fitted
TP5: MISO; TestPoint_Pad_D1.0mm; not fitted
TP6: MOSI; TestPoint_Pad_D1.0mm; not fitted
TP7: SCK; TestPoint_Pad_D1.0mm; not fitted
TP8: CS2; TestPoint_Pad_D1.0mm; not fitted
TP9: CS3; TestPoint_Pad_D1.0mm; not fitted
TP10: CHK; TestPoint_Pad_D1.0mm; not fitted
TP17: INT; TestPoint_Pad_D1.0mm; not fitted
TP18: LDI; TestPoint_Pad_D1.0mm; not fitted
TP19: TMP; TestPoint_Pad_D1.0mm; not fitted
TP20: PWM; TestPoint_Pad_D1.0mm; not fitted
TP21: Z; TestPoint_Pad_D1.0mm; not fitted
TP22: ADC; TestPoint_Pad_D1.0mm; not fitted
TP27: L; TestPoint_Pad_D1.0mm; not fitted
TP28: R; TestPoint_Pad_D1.0mm; not fitted
U5: 24CSM01; SOIC-8_5.3x5.3mm_P1.27mm; Digikey 24CSM01T-E/ST
U6: 23K256; SOIC-8_3.9x4.9mm_P1.27mm; Digikey 23K256-I/SN
U7: 74HC4051; SOIC-16_3.9x9.9mm_P1.27mm; Digikey CD74HC4051QM96Q1
U8: MMA8452Q; QFN_16_3x3x1mm_P0.5mm; Digikey MMA8452QT
U9: AT25DF641A; SOIC-8_5.3x5.3mm_P1.27mm; Digikey AT25DF641A-SH-B
U10: TC1046; SOT-23; Digikey TC1046VNBTR

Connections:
+3V3: BZ1.1 (-), C16.2, C17.2, C18.2, C19.2, C23.1, C24.2, C30.2, C31.2, J3.1 (V+), J3.4 (H+~), J8.4 (VDD), LCD1.6 (VCC), Q2.3 (E), R10.1, R11.1, R12.1, R13.1, R14.1, R15.1, R16.1, R17.1, R20.1, R21.1, R25.1, R55.1, R57.1, R58.1, R59.1, U5.8 (VCC), U6.7 (HOLD), U6.8 (VDD), U7.16 (VCC), U8.1 (VDDIO), U8.14 (VDD), U9.3 (WP), U9.7 (HOLD), U9.8 (VDD), U10.1 (+VS); also elsewhere on the board
/JOYSTICK, BUTTONS & SENSES/Button_A: R10.2, SW1.1, U7.14 (A1)
/JOYSTICK, BUTTONS & SENSES/Button_B: R11.2, SW2.4, U7.15 (A2)
/JOYSTICK, BUTTONS & SENSES/Button_L: R16.2, SW5.2, TP27.1, U7.5 (A5)
/JOYSTICK, BUTTONS & SENSES/Button_R: R15.2, SW6.1, TP28.1, U7.12 (A3)
/JOYSTICK, BUTTONS & SENSES/Button_X: R13.2, SW3.3, U7.13 (A0)
/JOYSTICK, BUTTONS & SENSES/Button_Y: R17.2, SW4.3, U7.1 (A4)
/JOYSTICK, BUTTONS & SENSES/Ligth: LCD1.7 (LED), Q2.2 (C)
ADC_CH0: C22.2, TP22.1, U7.3 (A); also elsewhere on the board
BUTTON_Z: J3.7 (B+), R20.2, TP21.1; also elsewhere on the board
GLCD_MISO: R7.2; also elsewhere on the board
GLCD_MOSI: R29.2; also elsewhere on the board
GLCD_PWM: R28.1; also elsewhere on the board
GLCD_SCK: R54.2; also elsewhere on the board
GLCD_SS: R5.2; also elsewhere on the board
GND: C16.1, C17.1, C18.1, C19.1, C20.1, C22.1, C23.2, C24.1, C25.1, C26.1, C27.1, C28.1, C30.1, C31.1, J3.3 (V-), J3.6 (H-), J3.8 (B-), J3.9 (SHIELD), J8.6 (VSS), J8.P1 (SHIELD), J8.P2 (SHIELD__1), J8.P3 (SHIELD__2), J8.P4 (SHIELD__3), J8.SWB (A), LCD1.2 (SCE), LCD1.8 (GND), Q1.3 (C), R23.2, SW1.3, SW1.4, SW2.1, SW2.2, SW3.1, SW3.2, SW4.1, SW4.2, SW5.1, SW6.2, U5.1 (A0), U5.2 (A1), U5.3 (A2), U5.4 (GND), U5.7 (WP), U6.4 (VSS), U7.6 (~E), U7.7 (VEE), U7.8 (GND), U8.5 (GND), U8.7 (SAO), U8.10 (GND), U8.12 (GND), U9.4 (GND), U10.3 (GND); also elsewhere on the board
INT_MG: R55.2, TP17.1, U8.11 (INT1); also elsewhere on the board
JOYSTICK_AXIS_X: C27.2, J3.5 (H), U7.4 (A7)
JOYSTICK_AXIS_Y: C26.2, J3.2 (V), U7.2 (A6)
MFS_CS: R58.2, TP8.1, U9.1 (CE#); also elsewhere on the board
MUX_A: U7.11 (S0); also elsewhere on the board
MUX_B: U7.10 (S1); also elsewhere on the board
MUX_C: U7.9 (S2); also elsewhere on the board
unnamed: BZ1.2 (+), Q1.2 (E)
unnamed: LCD1.5 (CLK), R54.1
unnamed: LCD1.3 (DC), R7.1
unnamed: LCD1.4 (DIN), R29.1
unnamed: LCD1.1 (RES), R5.1
unnamed: Q1.1 (B), R27.1
unnamed: Q2.1 (B), R28.2
unnamed: R21.2, R22.1
unnamed: C20.2, U8.2 (BYP)
unnamed: R24.2, U10.2 (Vout)
OUTPUT_BUZZER: R27.2, TP20.1; also elsewhere on the board
SCL: R14.2, TP3.1, U5.6 (SCL), U8.4 (SCL); also elsewhere on the board
SDA: R12.2, TP2.1, U5.5 (SDA), U8.6 (SDA); also elsewhere on the board
SENSE_LIGHT: C25.2, R22.2, R23.1, TP18.1; also elsewhere on the board
SENSE_TEMP: C28.2, R24.1, TP19.1; also elsewhere on the board
SPI_MISO: J8.7 (DAT0), TP5.1, U6.2 (SO), U9.2 (SO); also elsewhere on the board
SPI_MOSI: J8.3 (CMD), TP6.1, U6.5 (SI), U9.5 (SI); also elsewhere on the board
SPI_SCK: J8.5 (CLK), TP7.1, U6.6 (SCK), U9.6 (SCK); also elsewhere on the board
SRM_CS: R57.2, TP4.1, U6.1 (CS); also elsewhere on the board
USD_CK: J8.SWA (B), R25.2, TP10.1; also elsewhere on the board
USD_SS: J8.2 (CD/DAT3), R59.2, TP9.1; also elsewhere on the board

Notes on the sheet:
MULTIPLEXER LOGIC ANALOG
MEMORY EEPROM
ACCELEROMETER SENSE
MEMORY SRAM
SOCKET MICRO SD SPI CONNECTION
SENSE TEMPERATURE
CONTROL BUZZER
THUMB JOYSTICK
MEMORY FLASH
SENSE LIGTH LDR
GLCD SPI CONNECTION
